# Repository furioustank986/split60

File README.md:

# split60
The Split60 is Huskeyboard's first full keyboard, meaning that it uses a unique case. The cases are designed to be able to combine and look like a normal 60% keyboard, although a cable will still need to connect the two halves. It is a sandwich mount case; linear switches are recommended.

The Split60 uses the traditional ANSI 60% layout, except that the spacebar is divided into 2.25u/1.25u/2.75u segments to allow the keyboard to be split.

Eight m3x0.5 * 10mm screws will be required for assembly.

The two halves are connected by a USB C-to-C cable using an i2c connection.

The keyboard uses the ATmega32u4 chip.

The keyboard does not come with any LEDs.

The typing angle is 7 degrees.

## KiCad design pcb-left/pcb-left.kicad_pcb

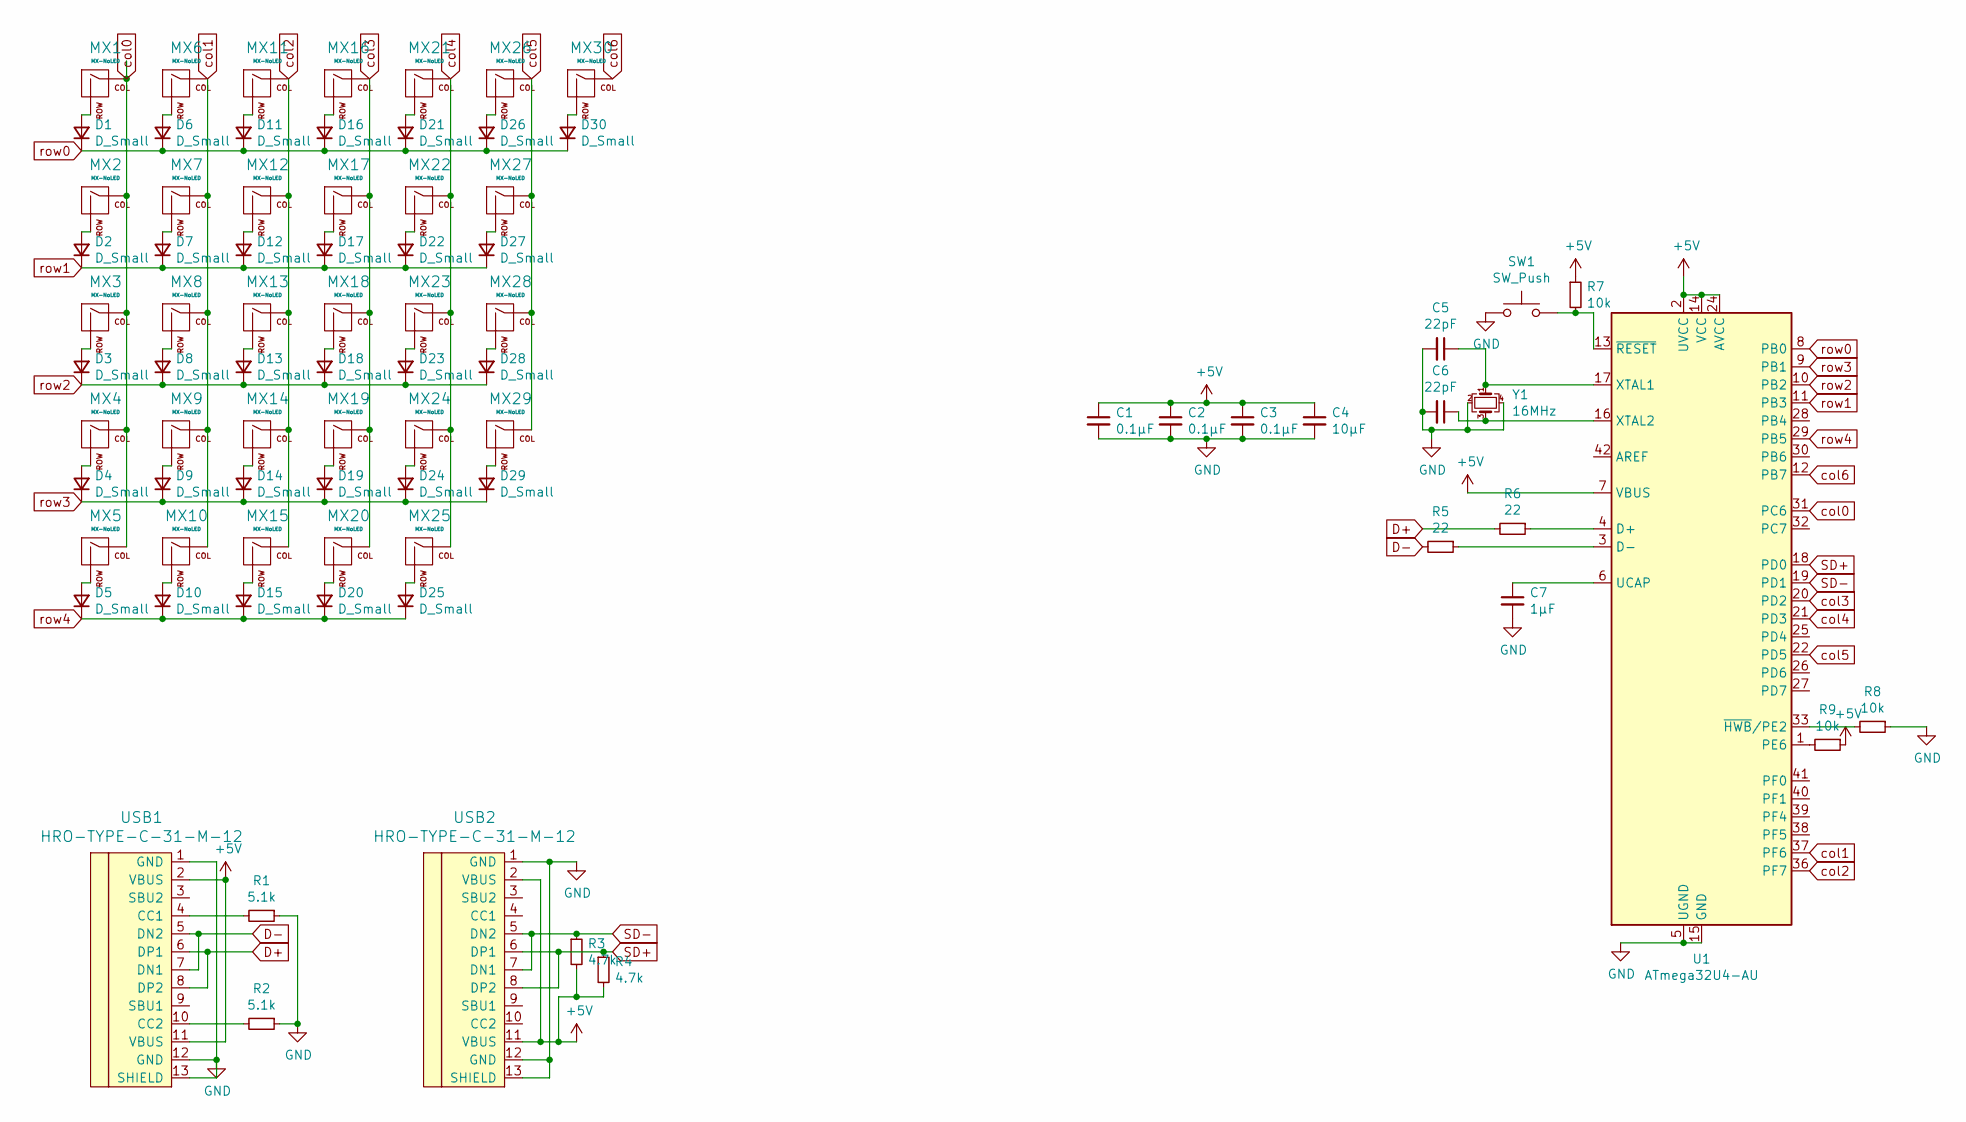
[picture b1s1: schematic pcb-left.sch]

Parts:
C1, C2, C3: 0.1µF; C_0805_2012Metric
C4: 10µF; C_0805_2012Metric
C5, C6: 22pF; C_0805_2012Metric
C7: 1µF; C_0805_2012Metric
D1, D2, D3, D4, D5, D6, D7, D8, D9, D10, D11, D12, D13, D14, D15, D16, D17, D18, D19, D20, D21, D22, D23, D24, D25, D26, D27, D28, D29, D30: D_Small; D_SOD-123
MX1, MX6, MX7, MX8, MX9, MX11, MX12, MX13, MX14, MX16, MX17, MX18, MX19, MX21, MX22, MX23, MX24, MX26, MX27, MX28, MX29, MX30: MX-NoLED; MXOnly-1U-NoLED
MX2: MX-NoLED; MXOnly-1.5U-NoLED
MX3: MX-NoLED; MXOnly-1.75U-NoLED
MX4, MX20: MX-NoLED; MXOnly-2.25U-NoLED
MX5, MX10, MX15, MX25: MX-NoLED; MXOnly-1.25U-NoLED
R1, R2: 5.1k; R_0805_2012Metric
R3, R4: 4.7k; R_0805_2012Metric
R5, R6: 22; R_0805_2012Metric
R7, R8, R9: 10k; R_0805_2012Metric
SW1: SW_Push; SKQG-1155865
U1: ATmega32U4-AU; TQFP-44_10x10mm_P0.8mm
USB1, USB2: HRO-TYPE-C-31-M-12; HRO-TYPE-C-31-M-12-Assembly
Y1: 16MHz; Crystal_SMD_3225-4Pin_3.2x2.5mm

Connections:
+5V: C1.1, C2.1, C3.1, C4.1, R3.2, R4.2, R7.1, R9.1, U1.2 (UVCC), U1.7 (VBUS), U1.14 (VCC), U1.24 (AVCC), U1.34 (VCC), U1.44 (AVCC), USB1.2 (VBUS), USB1.11 (VBUS), USB2.2 (VBUS), USB2.11 (VBUS)
D+: R6.2, USB1.6 (DP1), USB1.8 (DP2)
D-: R5.2, USB1.5 (DN2), USB1.7 (DN1)
GND: C1.2, C2.2, C3.2, C4.2, C5.2, C6.2, C7.2, R1.1, R2.1, R8.1, SW1.1, U1.5 (UGND), U1.15 (GND), U1.23 (GND), U1.35 (GND), U1.43 (GND), USB1.1 (GND), USB1.12 (GND), USB1.13 (SHIELD), USB2.1 (GND), USB2.12 (GND), USB2.13 (SHIELD), Y1.2, Y1.4
unnamed: C5.1, U1.17 (XTAL1), Y1.1
unnamed: C6.1, U1.16 (XTAL2), Y1.3
unnamed: C7.1, U1.6 (UCAP)
unnamed: D1.2 (A), MX1.2 (ROW)
unnamed: D2.2 (A), MX2.2 (ROW)
unnamed: D3.2 (A), MX3.2 (ROW)
unnamed: D4.2 (A), MX4.2 (ROW)
unnamed: D5.2 (A), MX5.2 (ROW)
unnamed: D6.2 (A), MX6.2 (ROW)
unnamed: D7.2 (A), MX7.2 (ROW)
unnamed: D8.2 (A), MX8.2 (ROW)
unnamed: D9.2 (A), MX9.2 (ROW)
unnamed: D10.2 (A), MX10.2 (ROW)
unnamed: D11.2 (A), MX11.2 (ROW)
unnamed: D12.2 (A), MX12.2 (ROW)
unnamed: D13.2 (A), MX13.2 (ROW)
unnamed: D14.2 (A), MX14.2 (ROW)
unnamed: D15.2 (A), MX15.2 (ROW)
unnamed: D16.2 (A), MX16.2 (ROW)
unnamed: D17.2 (A), MX17.2 (ROW)
unnamed: D18.2 (A), MX18.2 (ROW)
unnamed: D19.2 (A), MX19.2 (ROW)
unnamed: D20.2 (A), MX20.2 (ROW)
unnamed: D21.2 (A), MX21.2 (ROW)
unnamed: D22.2 (A), MX22.2 (ROW)
unnamed: D23.2 (A), MX23.2 (ROW)
unnamed: D24.2 (A), MX24.2 (ROW)
unnamed: D25.2 (A), MX25.2 (ROW)
unnamed: D26.2 (A), MX26.2 (ROW)
unnamed: D27.2 (A), MX27.2 (ROW)
unnamed: D28.2 (A), MX28.2 (ROW)
unnamed: D29.2 (A), MX29.2 (ROW)
unnamed: D30.2 (A), MX30.2 (ROW)
unnamed: R1.2, USB1.4 (CC1)
unnamed: R2.2, USB1.10 (CC2)
unnamed: R5.1, U1.3 (D-)
unnamed: R6.1, U1.4 (D+)
unnamed: R7.2, SW1.2, U1.13 (~RESET)
unnamed: R8.2, U1.33 (~HWB~/PE2)
unnamed: R9.2, U1.1 (PE6)
SD+: R4.1, U1.18 (PD0), USB2.6 (DP1), USB2.8 (DP2)
SD-: R3.1, U1.19 (PD1), USB2.5 (DN2), USB2.7 (DN1)
col0: MX1.1 (COL), MX2.1 (COL), MX3.1 (COL), MX4.1 (COL), MX5.1 (COL), U1.31 (PC6)
col1: MX6.1 (COL), MX7.1 (COL), MX8.1 (COL), MX9.1 (COL), MX10.1 (COL), U1.37 (PF6)
col2: MX11.1 (COL), MX12.1 (COL), MX13.1 (COL), MX14.1 (COL), MX15.1 (COL), U1.36 (PF7)
col3: MX16.1 (COL), MX17.1 (COL), MX18.1 (COL), MX19.1 (COL), MX20.1 (COL), U1.20 (PD2)
col4: MX21.1 (COL), MX22.1 (COL), MX23.1 (COL), MX24.1 (COL), MX25.1 (COL), U1.21 (PD3)
col5: MX26.1 (COL), MX27.1 (COL), MX28.1 (COL), MX29.1 (COL), U1.22 (PD5)
col6: MX30.1 (COL), U1.12 (PB7)
row0: D1.1 (K), D6.1 (K), D11.1 (K), D16.1 (K), D21.1 (K), D26.1 (K), D30.1 (K), U1.8 (PB0)
row1: D2.1 (K), D7.1 (K), D12.1 (K), D17.1 (K), D22.1 (K), D27.1 (K), U1.11 (PB3)
row2: D3.1 (K), D8.1 (K), D13.1 (K), D18.1 (K), D23.1 (K), D28.1 (K), U1.10 (PB2)
row3: D4.1 (K), D9.1 (K), D14.1 (K), D19.1 (K), D24.1 (K), D29.1 (K), U1.9 (PB1)
row4: D5.1 (K), D10.1 (K), D15.1 (K), D20.1 (K), D25.1 (K), U1.29 (PB5)

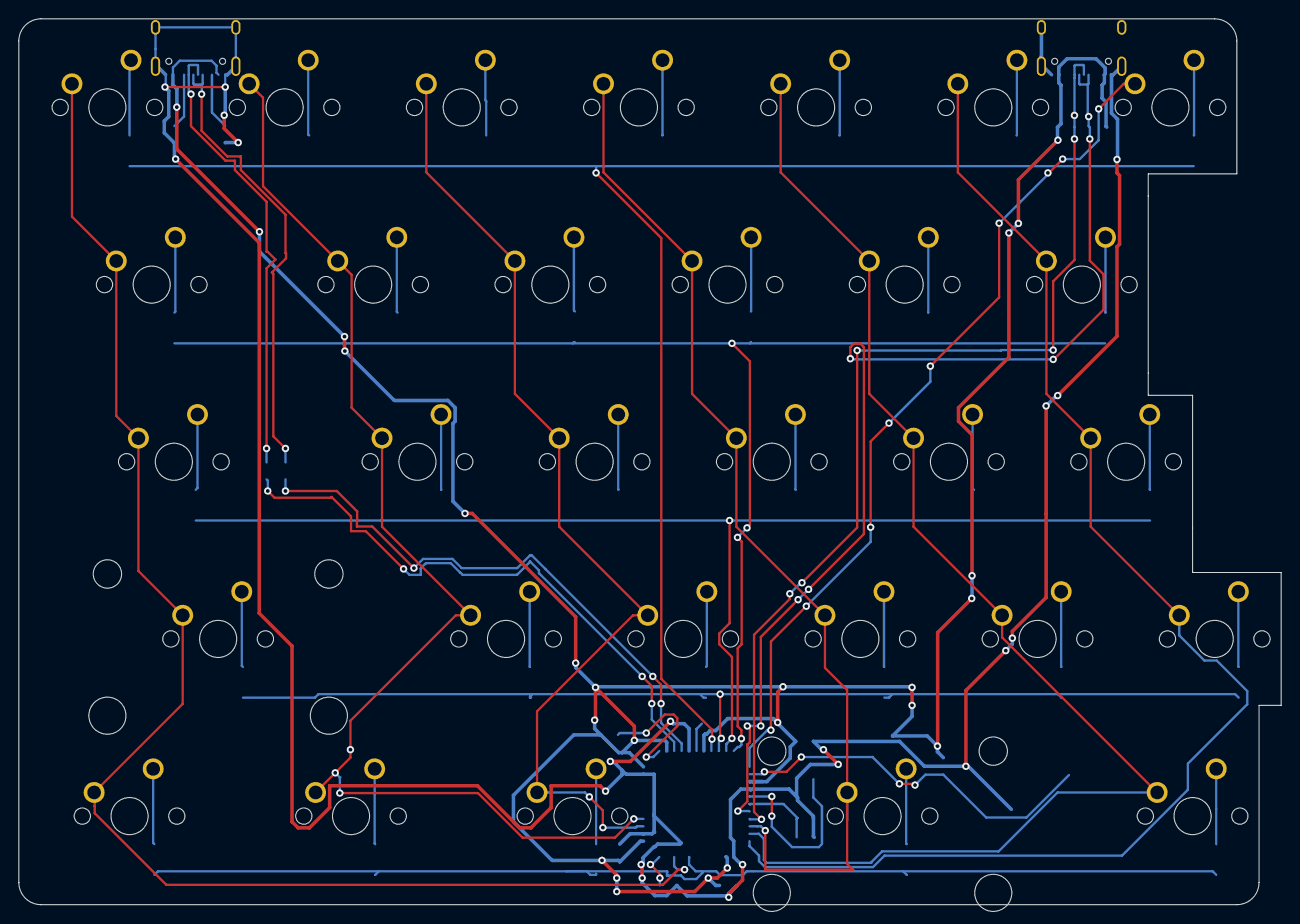
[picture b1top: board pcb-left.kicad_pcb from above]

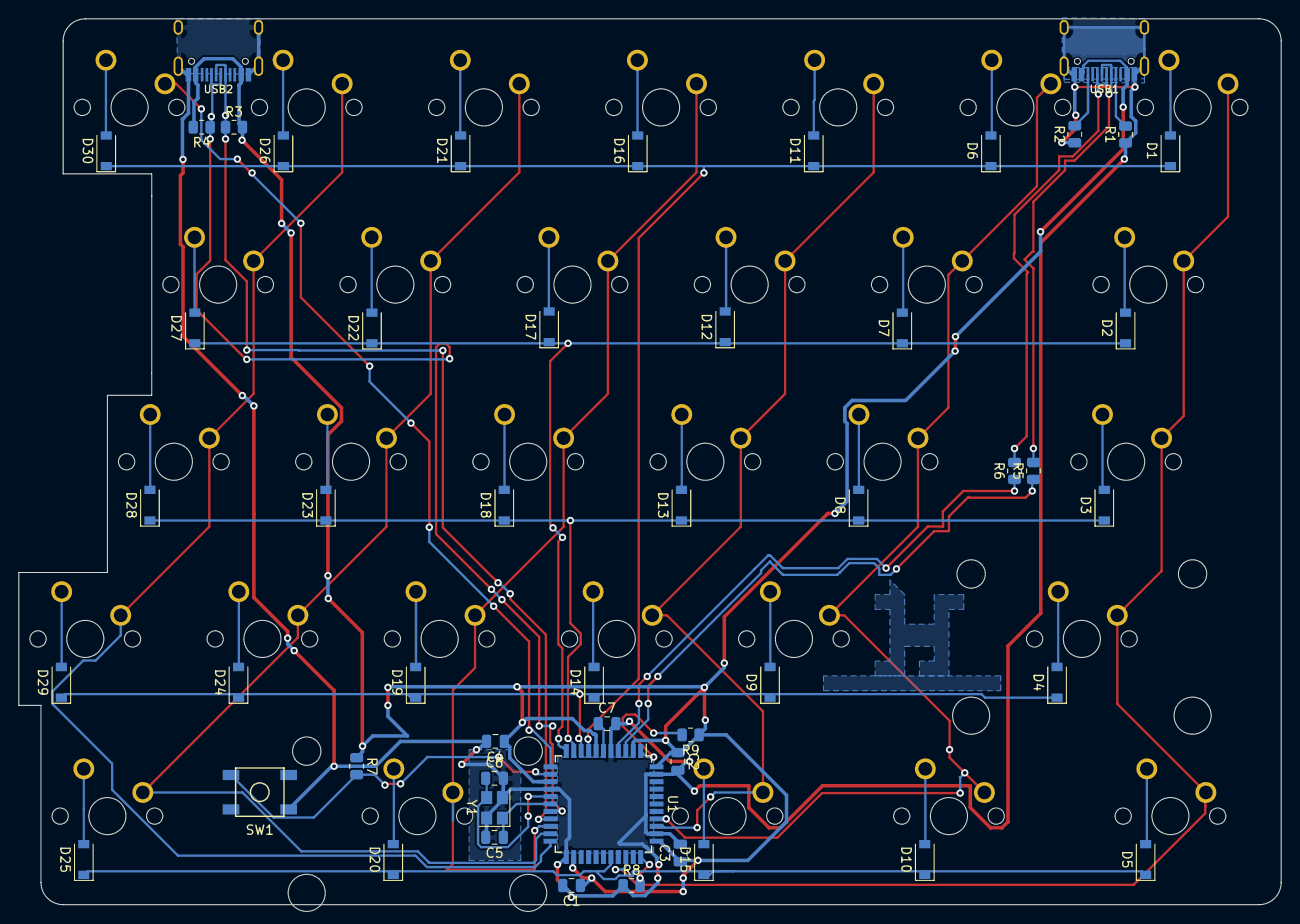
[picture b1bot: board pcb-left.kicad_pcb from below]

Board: 2 copper layers, 135.7 x 95.2 mm, 81 parts (51 on the bottom side), 58 nets.

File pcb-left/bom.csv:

"Id";"Designator";"Package";"Quantity";"Designation";"Supplier and ref";
1;"MX19,MX28,MX27,MX30,MX21,MX29,MX26,MX24,MX23,MX22,MX18,MX17,MX16,MX14,MX13,MX12,MX11,MX9,MX8,MX7,MX6,MX1";"MXOnly-1U-NoLED";22;"MX-NoLED";;;
2;"R9,R8,R7";"R_0805_2012Metric";3;"10k";;;
3;"MX20,MX4";"MXOnly-2.25U-NoLED";2;"MX-NoLED";;;
4;"MX15,MX25,MX10,MX5";"MXOnly-1.25U-NoLED";4;"MX-NoLED";;;
5;"Y1";"Crystal_SMD_3225-4Pin_3.2x2.5mm";1;"16MHz";;;
6;"USB2,USB1";"HRO-TYPE-C-31-M-12-Assembly";2;"HRO-TYPE-C-31-M-12";;;
7;"U1";"TQFP-44_10x10mm_P0.8mm";1;"ATmega32U4-AU";;;
8;"SW1";"SKQG-1155865";1;"SW_Push";;;
9;"R6,R5";"R_0805_2012Metric";2;"22";;;
10;"R4,R3";"R_0805_2012Metric";2;"4.7k";;;
11;"R2,R1";"R_0805_2012Metric";2;"5.1k";;;
12;"MX3";"MXOnly-1.75U-NoLED";1;"MX-NoLED";;;
13;"MX2";"MXOnly-1.5U-NoLED";1;"MX-NoLED";;;
14;"D30,D29,D28,D27,D26,D25,D24,D23,D22,D21,D20,D19,D18,D17,D16,D15,D14,D13,D12,D11,D10,D9,D8,D7,D6,D5,D4,D3,D2,D1";"D_SOD-123";30;"D_Small";;;
15;"C7";"C_0805_2012Metric";1;"1µF";;;
16;"C6,C5";"C_0805_2012Metric";2;"22pF";;;
17;"C4";"C_0805_2012Metric";1;"10µF";;;
18;"C3,C2,C1";"C_0805_2012Metric";3;"0.1µF";;;

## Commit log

2022-06-16 added base files for case and plate
2022-06-16 added case and screw holes. TODO: Connector holes
2022-06-16 added submoddules
2022-06-16 added schematic for left PCB
2022-06-16 Added proper screw holes and feet holes
2022-06-16 added pcb files
2022-06-17 finished left side pcb
2022-06-17 finalized left side pcb
2022-06-17 added right side pcb
2022-06-17 added files for manufacturing right side pcb
2022-06-17 added production files for left pcb
2022-06-17 firmware
2022-06-18 fixed errors/warnings
2022-06-18 re-zoned crystal area
2022-06-18 added schematics as png for easy reference
2022-06-18 added step files
2022-06-18 added f3d
2022-06-18 fixed crystal zone
2022-06-18 added more case design concepts
2022-06-18 added fillet
2022-06-21 added commodore 64
2023-11-08 fix: Compile on the latest QMK.
